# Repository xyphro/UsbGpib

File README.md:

# Table of contents

:newspaper: [Latest updates](Updates.md)
<br> :hammer: [Buy it or build it](#buy-it-or-build-it)
<br> :wave: [UsbGpib Introduction](#usbgpib-introduction)
<br> :house: [Housing / Enclosure](#housings)
<br> :computer: [Software](#software)
<br> &nbsp; &nbsp; :electric_plug: [Using the device](#using-the-device)
<br> &nbsp; &nbsp; :gear: [Setting and getting parameters](#setting-parameters)
<br> :heavy_check_mark: [Testing status](#testing-status)
<br> :notebook: [Tutorials](Tutorials/README.md) <- **New!**
<br> :heart: [Support the Project](#support-the-project)

# Summarized latest updates

For detailed visibility look under the Latest update link above!

[18th Apr 2026]: **Released Firmware V2.4: Added support for multiple GPIB devices**

[18th Apr 2026]: **Added some updated notes on GPIBee**

[07th Mar 2026]: **USbGpib V2 back in Stock on Elecrow**  

[07th Mar 2026]: **10 UsbGpib V3 == GPIBee prototypes ready for testing**

# Next version update USBGpib V3 

**UsbGpib V3 has a Name - Introducing GPIBee**

...and as you’ll see in the picture: The beauties are ready!

After months of development, redesigns, loosing hair on fixing SW bugs and teasing the new Ethernet + PoE capabilities, the next generation of UsbGpib finally has its official identity. From this point forward, UsbGpib V3 will be known as GPIBee - a compact, fast, and delightfully capable little worker that's ready to buzz around your lab equipment.

PoE is fully operational, VXI-11 supports multiple simultaneous connections, and USB High-Speed is performing flawlessly - on MY bench. Which does not mean (yet) on everybody elses bench. Testing is by multiple people is always very important!

I now have ten GPIBee prototypes fully assembled and sitting proudly on my desk. These units will soon head out to the first wave of beta testers who’ve been following the journey and are eager to put them through real‑world use.
I had hoped to start shipping next week, but with Embedded World taking up my entire schedule, distribution will begin shortly after I'm back. The excitement doesn't slow down - it just builds a little more.

Thank you all for the incredible support, feedback, and enthusiasm.

GPIBee is about to take its first flight, and you're part of the swarm that made it possible.
Stay tuned - beta testing starts soon, and the prototypes look fantastic.

## GPIBee update 18th April: 

The first prototypes have been shipped, and internal testing is already well advanced.  
Across all protocols, read performance shows a **3.5× to 5× speed increase**, and this is **without** any dedicated speed-optimization work applied yet.

## Communication Modes

### USB Interface

GPIBee supports three independent USB-based communication modes:

1. **Network mode**  
   GPIBee exposes a USB-based Ethernet interface. An IP address is assigned automatically, enabling true plug-and-play operation.  
   - Full **VXI-11** support  
   - Integrated **web server** providing configuration pages, a GPIB command console, and the complete manual matching the currently installed firmware  
   - Ideal for multi-device setups and remote control - it should be considered as the first Goto solution in terms of USB based modes.

2. **USBTMC mode**  
   Similar to **UsbGpib V2**, but extended with additional commands, including the ability to set the target **GPIB device address** — enabling communication with multiple GPIB instruments.

3. **++ protocol mode**  
   Exposes a **USB CDC UART** implementing the popular ++ protocol, compatible with existing controllers using that protocol — but at significantly higher speed.

The USB modes are **mutually exclusive**. The active mode can be selected via the **web interface** or through internal **SCPI commands**.

### Ethernet Interface

1. **VXI-11**  
   Provides multiple logical channels, allowing communication with several GPIB devices simultaneously without manually switching addresses between commands. 
   - Proper **lock handling** for multi-client access  
   - Full **SRQ** support  
   - Full **GPIB subaddressing** support

2. **++ protocol**  
   Optional **TCP/IP** service on port **1234**, offering the same `++` protocol implementation as in USB CDC UART mode.

Both Ethernet protocols can be **active at the same time**. The Ethernet interface also exposes the same **web interface** as USB network mode, enabling GPIB transfers, configuration changes, and access to the **firmware-synchronized manual**.

## GPIBee Beta Testing Status

The current beta focus remains on **functional correctness and stability**.  
**Speed optimization** will follow next.

For testers not having received an adapter yet: Additional prototype units will be shipped soon. Handling too many testers at once would otherwise become too **time-intensive**.

---

# Buy it or build it

* Tired of tinkering? Want to skip the hassle and get straight to using your GPIB setup?  
* You’d rather spend your time using your instruments instead of assembling hardware?

Skip the soldering iron and jump straight into your GPIB workflow!

You’ve got two solid options to get a ready‑to‑run UsbGpib adapter.

## &#x1f1fa;&#x1f1f8; - United States
* If you're in the US, you can now order the UsbGpibV2 directly from several sources, including my distribution partner Binho LLC. Enjoy fast domestic shipping with no long waits, no customs paperwork, and no surprises - just quick delivery and a smooth experience: 
<br> &#x1F449; <a href="https://binho.io/test-measurement/products/usbgpib-v2/" target="_blank">https://binho.io/test-measurement/products/usbgpib-v2/</a>
<br> &#x1F449; <a href="https://www.digikey.com/short/29nqq5cz" target="_blank"> https://www.digikey.com/short/29nqq5cz</a>
<br> &#x1F449; Amazon US also has it listed, but right now no stock, but worthwhile to check it out there too.

## &#x1F30E; - Worldwide
* I’ve teamed up with Elecrow to bring you ready-to-roll GPIB-USB converters – perfect for those who want results, not a weekend project.
* These adapters come fully assembled, programmed, housed, tested, and ready to go. No fuss. No build. Just plug it in and start working.
* The Adapters match 100% the V2 version described in this repository. 
* &#x1F449; <a href="https://www.elecrow.com/xyphrolabs-gpibusb.html" target="_blank">https://www.elecrow.com/xyphrolabs-gpibusb.html</a>

Let the data flow begin!

This doesn’t mean I’m going fully commercial - far from it.
Offering pre-built adapters is simply a convenience for those who’d rather skip the build and get straight to using their gear.

All sharing, support, and collaboration will remain fully open, just as before.
This is about choice, not change!

The full design files are located in this repository in case you want to build the devices yourself.

---

# UsbGpib Introduction
Versatile, cheap, portable and robust USB to GPIB converter (USBTMC class based).

You'll find many projects like this, but this one is special (ok, everybody will claim this) :-)

V1 Hardware: 

V2 Hardware: 

If you have a lot of test equipment at home, you might know the issues: Lots of devices only have GPIB as interface and the GPIB adapters and GPIB cables on the market are very expensive and some of them even have many issues, when run under Windows 10 (device driver does not work). Or they e.g. are not able to be operated with VISA, because they are UART based, need special command sequences, ...

The adapters are also typically very long, such that they extend the overall length of your test equipment by at least 10cm (~4 inches).

Apart of the 2 very big manufacturers, other GPIB adapters, e.g. with Ethernet or also USB interface are not recognized by normal VISA providers or PyVisa, making the measurement control implementation specific for your GPIB adapter.

I've got frustrated and tried to turn it into something positive. Here a video showing the final device in action - click to view:

Some goals of the project were:
- Work based on the standard USBTMC protocol. This allows the GPIB test equipment to look like a normal USB based measurement device and work flawless with e.g. NI VISA, Labview, Matlab or PyVisa.
- Have a small length - otherwise my equipment has the risk of falling from the shelf :-) Also the USB cable should connect 90 degree angled, to make it very short. With V2 HW, the length got further reduced to the size of a GPIB connector.
- It should be cheap but still versatile (you can build a single one of these for only 14 USD!)
- It should support ALL my test equipment, from many different GPIB implementation generations and different GPIB flavors
- The Firmware should be upgradeable over USB
- It should be rock-solid (!) I don't want to end up in a very long measurement being interrupted because of a software issue of my USB GPIB converter.
- It should support additional features like serial poll, remote enabling/disabling
- If there is no GPIB device connected to the USBGpib converter, or the GPIB device is powered down, there should be no USB device visible on the PC.

All those goals are met.

---

# Hardware

## Microcontroller choice

Although I typically would prefer nowadays an ARM Cortex M0/3/4/7 controller, there is an issue with it. Available devices support only max. 3.3V supply voltages, such that there would be a requirement for a level-shifter towards the GPIB Bus.
GPIB is based on 5V (not exactly true, but a first iteration).

This limited the microcontroller choice to e.g. AVR or PIC controllers. Because of very good availability I ended up in ATMEGA32U4 controllers.
Apart of the device supporting 5V I/O voltages, it also does not require a regulator to be part of the application - it has an internal 3.3V regulator. This minimizes the full application schematic and BOM.

Apart from that, there is an excellent USB stack available [http://www.fourwalledcubicle.com/LUFA.php](http://www.fourwalledcubicle.com/LUFA.php).

The GPIB side of the schematic can be directly connected to the ATMega32U4 IO pins. The IO pins from the microcontroller side are only set to 2 different states: Tri-state (input) or output LOW, to talk over GPIB.

## Component sourcing

All components are easy to source, so I only specify the potential critical ones:

- 16 MHz Crystal: Farnell 2853867 - MCSJK-7E-16.00-8-30-100-B-30 
- REV 1 GPIB connector: Farnell 2421095 - NORCOMP 112-024-113R001. For REV 2 use a straight 24P male solder type connector e.g. from AliExpress.
- USB connector for V1 HW: Farnell 2668483 - Amphenol ICC 61729-1011BLF
- USB connector for V2 HW: Best is to look on AliExpress for 57 series 24P connector as a starting point.

## PCB

The PCB can be ordered at nearly any PCB pool production service (e.g. 10 PCBs for 2 USD + shipping). The gerber files are included in the "HW/Gerber files" subdirectory.

## Mounting the PCB & Flashing the firmware

The PCB is available in 2 revisions.
- [REV 1](HW/REV1/README.md) is the most popularly used right now due to age. It has a USB Type-B connector and an L-shaped housing visible on a few photos of this page.
- [REV 2](HW/REV2/README.md) has some improvements like being smaller, better fit and USB Type-C connector.
- A REV 3 is upcoming. It will be a major redesign with more speed, Ethernet and power over Ethernet support, but the same DNA: Standard protocols being used and ensure compatibility and stability!

Choose whatever you prefer. The software images, but also the external behavior is the same.

---

# Housings

## REV 1

I created a sophisticated 3D printable housing for this adapter. The design was made with Fusion 360. The project file + the STL files are included in the "Housing" sub directory.

The PCB fits perfectly into it. Optionally it can be fixed with 2 mounting screws (the GPIB connector has 2 threads, use 2 times 4-40 UNC x 3/8) and the TOP cover snaps onto the housing base.

I printed this using an Ender 5 3D printer with black PLA, 0.15mm layer height, 1mm wall thickness, no support.
Take care, that you rotate the TOP part of the housing by 180 degrees, so that the flat side is located on the printer bed.
Printing works fine, several iterations of the design were made to ensure good printability.
I printed so far 15 housings, without a single fail.

More information on this REV 1 can be found here: [REV 1](HW/REV1/README.md).
Note, that also the programming/build instructions moved to this location.

## REV 2

The REV 2 housing is a lot smaller, but requires 2 screws.
The housing is quite important to be able to connect and disconnect the board without breaking anything. It is key for mechanical stability of the adapter.
When operating the device without housing, take very well care when plugging in and out the board in case the GPIB connector has a very tight fit.

Information on how to build it can be found in the HW/REV 2 folder: [REV 2](HW/REV2/README.md).
Note, that also the programming/build instructions moved to this location.

---

# Software

## Source code

The source code of the Boot loader (slightly modified LUFA MassStorage Boot loader) and the main USBGPIB converter are located in the "SW" subdirectory.
At the time of publication LUFA 170418 release was used, with GCC as compiler.

Note: The Software is compatible with any HW revision in this repository. For REV 1 and REV 2 hardware you don't need different SW images.

## Binaries

For those, that just want to create their own device, I've included the binary output in the "SW/binaries" subdirectory.

---

# Using the device

## USB enumeration

You might be surprised initially, that the device does not show up in your device manager (or lsusb), when you connect only the USB side. This is a feature, not a bug (really!).
Only, if a GPIB device is connected, you can see the device on your PC too.

The reason behind the feature is simple: Instead of having a standard GPIB wiring, where you have a single GPIB controller and lots of GPIB devices interconnected, USBGPIB supports only a direct connection of the USBGPIB device to your measurement device. If you have like me e.g. 14 Instruments you don't want all to show up in the device manager, if the measurement device itself is powered down - you won't anyway be able to communicate with a powered down device.

When USB and the GPIB side is connected, the device enumerates. The USBGPIB device reads out the ID of the instrument and constructs a unique USB Serial number out of it. It is thus easily possible to assiate multiple connected USBGPIB devices with the measurement instrument.

The VISA ressource name is constructed from this USB Serial number. You can identify easily e.g. in NiMax, which device is connected:

If you connect your USBGPIB device afterwards to another GPIB measurement device, it will disconnect and connect with a new serial number string, matching the other GPIB device *IDN? response again.

## GPIB settings on your measurement device

GPIBUSB does probe all GPIB primary addresses (and secondary address 0) for presence of a GPIB Talker/listener. It is thus not required to set a specific GPIB address - GPIBUSB will find it itself.

The only importance setting on the measurement device is, that the GPIB interface is enabled, which is typically the case.

## LED indicator

The LED indicates different states:

LED blinking: The USBGPIB converter is connected to a measurement instrument, it is powered off or its GPIB port is disabled. In this state, the device is also not connected to USB and will not show up in the device manager or lsusb.
LED on: The device is connected to a measurement device and GPIB communication possible. It is also accessible over USB
LED off: The device is not connected over USB, or the PC powered off :-)

## Controlling GPIB devices

As this converter implements the standard USBTMC Test and measurement class, you can control your instrument from ANY of the normal VISA tools. I tried so far R&S VISA and NI Visa, using Python and Matlab to talk to the devices.

# Testing status

This project is actively maintained since more than 6 years and I personally consider it as very stable. It is proven by multiple users to operate on MacOSX, Linux and Windows and measurement equipment from several decades.

In general I take bug reports very serious and want to "fix them all". In case you don't get an answer on-time on items you report in the issues section, please write me: Xyphro@gmail.com. 
I often miss seeing issue reports very quickly, as I don't get an email once they are filed.

## Sucessfully tested measurement equipment:

Below list is equipment I mainly myself tested. Many other users have other measurement equipment proven in use already.

- R&S FSEM30
- R&S SMIQ03
- R&S CMU200
- R&S SMW200A
- R&S FSW
- R&S FSV
- Keithley 199 multimeter
- HP 34401 DMM from different generations / with different FW versions
- HP 3325A synthesizer/frequency generator
- HP 3457A multimeter
- Agilent E4406A VSA transmitter tester
- Tektronix TDS7104 Digital Phosphor Oscilloscope
- HP 8596A spectrum analyzer
- Agilent E3648A dual power supply

## Scenarious

- It works under all popular operating systems like Windows 7 and 10, 11, Linux and MacOSX
- USB1.1, USB2.0 and USB3.x ports tested, with and without USB HUB in between.
- The connection stays responsive, when power cycling the PC, or hibernating/sleeping it
- Different connection cycles (GPIB side connected first, USB side connected first, swapping GPIB side equipment, ...)
- Extensive testing of timeout scenarious. E.g. making an illegal query and testing, if the USBTMC handles the timeouts properly. This was a very tricky part to get right.
- Tested special transfer modes. E.g. capturing screenshots from different equipment is usually something, which will drive other GPIB adapters to the limits, because binary data of unknown length needs to be transported successfully.

# Setting Parameters

The firmware version from 13th January 2024 onwards has the ability for human readable text base configuration of several parameters.
The previous methods are still supported, but won't be further documented. You can look them back in the history of this file.

The command parser is quite simple. For that reason follow the exact syntax as shown below. 
Don't add extra spaces or make other modifications or concatenate commands.

## Read termination method

While most GPIB interfaces use the hardware signal EOI to signal the end of a message, not all old equipment supports it. Some older instruments even don't have the EOI pin hardware wise wired and use \r or \n termination.

The USB-TMC standard allows to set the read termination. While in firmware versions before < 2.0 I did not enable that method, it is now finally supported with standard compliance.

I document here the older method (using pulse indicator request), but I add also the newer methods which are 100% UsbTmc compliant and portable across different equipments. You can choose which ones to use, but in some cases pulse indicator requests can be difficult to issue, for which reason it is likely better to use the standard compliant method.

### Set read termination to CR (\r):
(old method)
```
dev.control_in(0xa1, 0x40, 0, 0, 1); # USBTMC pulse indicator request (enables internal command processing)
dev.write('!term cr')
```
Above setting is volatile. To make this a permanent setting call the below mentioned "!term store" command.

(prefered method) Alternatively you can set the termination directly with visa means, e.g. using PyVisa:
```
dev.set_visa_attribute(visa.constants.VI_ATTR_TERMCHAR_EN, True)
dev.set_visa_attribute(visa.constants.VI_ATTR_TERMCHAR, ord('\r') )
```

### Set read termination to LF (\n):
(old method)
```
dev.control_in(0xa1, 0x40, 0, 0, 1); # USBTMC pulse indicator request (enables internal command processing)
dev.write('!term lf')
```
Above setting is volatile. To make this a permanent setting call the below mentioned "!term store" command.

(prefered method) Alternatively you can set the termination directly with visa means, e.g. using PyVisa:
```
dev.set_visa_attribute(visa.constants.VI_ATTR_TERMCHAR_EN, True)
dev.set_visa_attribute(visa.constants.VI_ATTR_TERMCHAR, ord('\n') )
```

### Set read termination to EOI only (default setting):
(old method) 
```
dev.control_in(0xa1, 0x40, 0, 0, 1); # USBTMC pulse indicator request (enables internal command processing)
dev.write('!term eoi')
```
Above setting is volatile. To make this a permanent setting call the below mentioned "!term store" command.

(prefered method) Alternatively you can set the termination directly with visa means, e.g. using PyVisa:
```
dev.set_visa_attribute(visa.constants.VI_ATTR_TERMCHAR_EN, False)
dev.set_visa_attribute(visa.constants.VI_ATTR_TERMCHAR, ord('\0') )
```

### Save readtermination setting in eeprom (make them non-volatile)
```
dev.control_in(0xa1, 0x40, 0, 0, 1); # USBTMC pulse indicator request (enables internal command processing)
dev.write('!term store')
```

Above relates to the "old non prefered method". In general it is a good idea to set the read termination volatile and use the above suggested methods highlighted with (prefered method).

### Query current termination setting from device
```
dev.control_in(0xa1, 0x40, 0, 0, 1); # USBTMC pulse indicator request (enables internal command processing)
print(dev.query('!term?'))
```
This returns a text string containing "lf", "cr" or "eoi"

## Multi-device support - Setting the GPIB device target address

Since Firmware version V2.4 USBGpib allows supporting multiple instruments.

While the USBTMC protocol allows only setting a single device to be addressed and composite USB devices are not well supported by all VISA implementations, I decided to add a command to set the address of the GPIB device which is addressed.

There is a minor limitation of this approach, which is that service request SRQ handling is only done properly to the currently selected GPIB device.
Another one is, that users shall never forget to set the GPIB address to the correct setting before issuing a command.

### Setting a primary address only

Substitute the text <Primary_address> with a number from 1 to 30 to set the primary address of the new GPIB device to talk to in following GPIB transactions

```
dev.control_in(0xa1, 0x40, 0, 0, 1);
dev.write('!addr <Primary_address>')
```

### Setting a primary + secondary address

Substitute the text <Primary_address> with a number from 1 to 30 to set the primary address and <Secondary_address> with a number from 0..6 or 96..102 of the new GPIB device to talk to in following GPIB transactions.
Note, that not the full subaddress range of 0..31 or 96..127 is supported as of now - this requires a bit more work. Most common device with subaddresses like R&S CMU200 only are well covered with that current range.

```
dev.control_in(0xa1, 0x40, 0, 0, 1);
dev.write('!addr <Primary_address> <Secondary_address>')
```
### Python wrapper example code for GPIB address setting

```
import pyvisa as visa
dev = 'USB0::0x03EB::0x2065::GPIB_22_14236333938351C00011::INSTR'
rm = visa.ResourceManager()
dev = rm.open_resource(dev, open_timeout=1000)

def set_gpib_addr(primary_address, secondary_address = None):
    dev.control_in(0xa1, 0x40, 0, 0, 1);
    if secondary_address is None:
        dev.write('!addr %d' % primary_address);
    else:
        dev.write('!addr %d %d' % (primary_address, secondary_address));
    
# Address CMU200, which is for me on primary address 1, secondary address 0
set_gpib_addr(1, 0)
print(dev.query('*IDN?'))

# address HP3457A on primary GPIB address 22
set_gpib_addr(22)
dev.write('END,ALWAYS')
print(dev.query('ID?'))
```

This code results in my current testsetup with CMU200 and HP3457A in this output:

```
Rohde&Schwarz,CMU 200-1100.0008.02,xxxxxx,V5.22

HP3457A
```

## AutoID setting

Default wise the GPIB adapter tries during power on of the instrument to query using *IDN? or ID? commands the instrument name automatically.
This is used to build the USB serial number, which finally gets part of the VISA ressource string.

Not all instruments support this *IDN / ID? query. For this reason this feature can be turned off.
The serial number will then be built based on the GPIB address of the instrument.

### Turn AutoID feature off
```
dev.control_in(0xa1, 0x40, 0, 0, 1); # USBTMC pulse indicator request (enables internal command processing)
dev.write('!autoid off')
```
This setting is stored in eeprom = non volatile memory, so will survive a power cycle

### Turn AutoID feature on
```
dev.control_in(0xa1, 0x40, 0, 0, 1); # USBTMC pulse indicator request (enables internal command processing)
dev.write('!autoid on')
```
This setting is stored in eeprom = non volatile memory, so will survive a power cycle

### turn auto ID on with delay

Some instruments need after turn on some seconds before GPIB is responsive.

With below 3 settings you can set a delay which is applied before the instrument ID is queried after power on.
Note that it will take then also more time, before the USB device is recognized by the PC.

Also this setting is non-volatile.

Delay 5 seconds:
```
dev.control_in(0xa1, 0x40, 0, 0, 1); # USBTMC pulse indicator request (enables internal command processing)
dev.write('!autoid slow')
```

Delay 15 seconds:
```
dev.control_in(0xa1, 0x40, 0, 0, 1); # USBTMC pulse indicator request (enables internal command processing)
dev.write('!autoid slower')
```

Delay 30 seconds:
```
dev.control_in(0xa1, 0x40, 0, 0, 1); # USBTMC pulse indicator request (enables internal command processing)
dev.write('!autoid slowest')
```

### read autoid setting

```
dev.control_in(0xa1, 0x40, 0, 0, 1); # 
print(dev.query('!autoid?'))
```
Returns as text string either: "off", "on", "slow", "slower" or "slowest".

## Firmware version

Finally I implemented a command to query the USB adapters firmware version :-)

```
dev.control_in(0xa1, 0x40, 0, 0, 1); # USBTMC pulse indicator request (enables internal command processing)
print(dev.query('!ver?'))
```

## Shorten ressource strings (Matlab)

A user discovered that Matlab has a limitation in the VISA ressource string length and shared a pull request to reduce the length.
I expose this now first time in the baseline firmware with the following options.

This setting is stored in eeprom = non volatile.

### Limit the USB serial number to a length of 20 characters
```
dev.control_in(0xa1, 0x40, 0, 0, 1); # USBTMC pulse indicator request (enables internal command processing)
dev.write('!string short')
```

### disable limitation of USB serial number length (default behavior)
```
dev.control_in(0xa1, 0x40, 0, 0, 1); # USBTMC pulse indicator request (enables internal command processing)
dev.write('!string normal')
```

### query the string length setting.
```
dev.control_in(0xa1, 0x40, 0, 0, 1); # USBTMC pulse indicator request (enables internal command processing)
print(dev.query('!string?'))
```

This returns as text string either "normal" or "short".

## reset the adapter
```
dev.control_in(0xa1, 0x40, 0, 0, 1); 
dev.write('!reset')
```

Do a reset of the adapter. Note that due to the reset you have to close the visa session and start a new one as the device re-enumerates on the USB.

---

# Support the project

Or support by buying a fully prebuilt adapter at: <a href="https://www.elecrow.com/xyphrolabs-gpibusb.html" target="_blank">https://www.elecrow.com/xyphrolabs-gpibusb.html</a>

In general any email, post or feedback is also very valuable, and don't feel bad if you don't use the support options :-)
Feel free to contact me at Xyphro@gmail.com

---

This page is from XyphroLabs UsbGpib project: <a href="https://github.com/xyphro/UsbGpib" target="_blank">https://github.com/xyphro/UsbGpib</a>

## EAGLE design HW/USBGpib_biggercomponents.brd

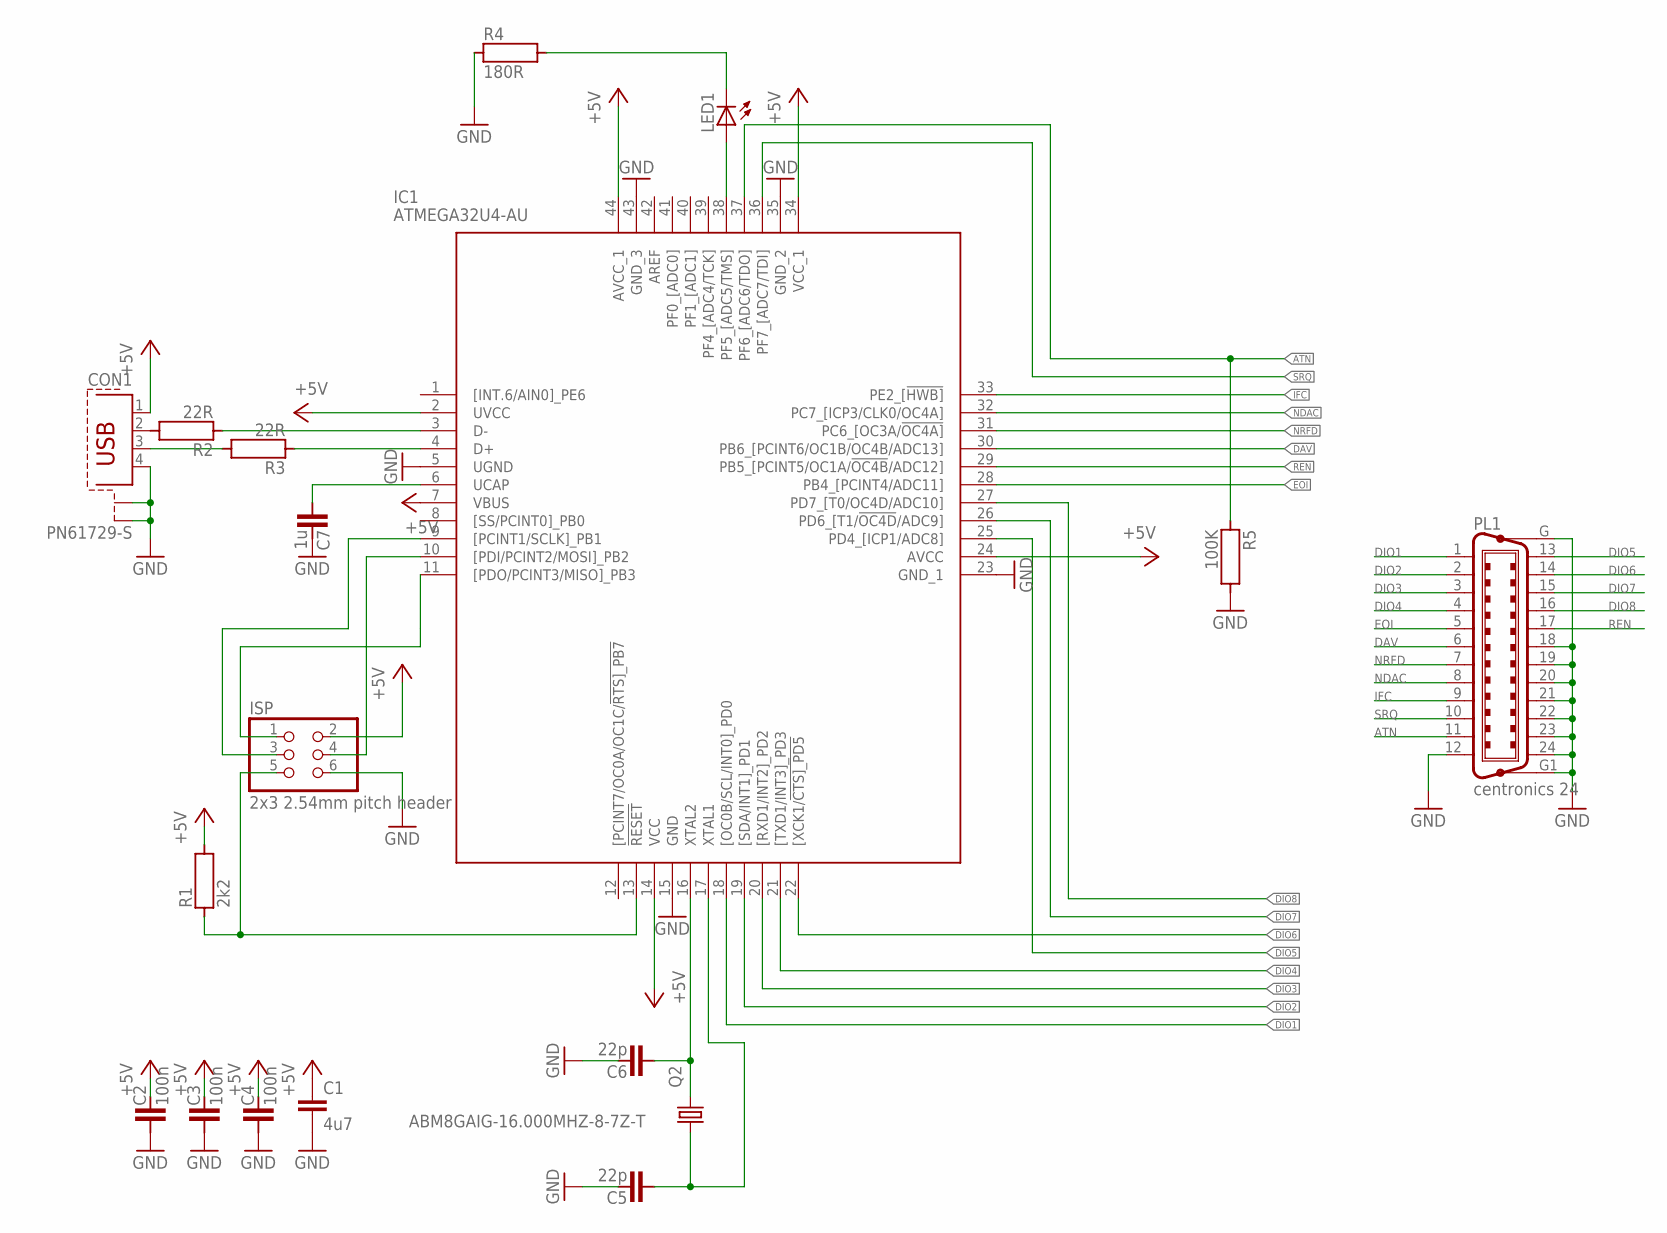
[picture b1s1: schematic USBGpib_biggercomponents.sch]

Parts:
C1: 4u7; C0805
C2, C3, C4: 100n; C0603
C5, C6: 22p; C0603
C7: 1u; C0603
CON1: PN61729-S
IC1: ATMEGA32U4-AU; QFP80P1200X1200X120-44N
ISP: 2x3 2.54mm pitch header; 2X03
LED1: LEDCHIPLED_1206; CHIPLED_1206
PL1: centronics 24; 24HP_MALE
Q2: ABM8GAIG-16.000MHZ-8-7Z-T; 3.2X2.5_KX-7
R1: 2k2; R0603
R2, R3: 22R; R0603
R4: 180R; R0603
R5: 100K; R0603

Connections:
+5V: C1.1, C2.2, C3.2, C4.2, CON1.1, IC1.2 (UVCC), IC1.7 (VBUS), IC1.14 (VCC), IC1.24 (AVCC), IC1.34 (VCC_1), IC1.44 (AVCC_1), ISP.2, R1.2
ATN: IC1.37 (PF6_[ADC6/TDO]), PL1.11, R5.1
DAV: IC1.30 (PB6_[PCINT6/OC1B/OC4B/ADC13]), PL1.6
DIO1: IC1.18 ([OC0B/SCL/INT0]_PD0), PL1.1
DIO2: IC1.19 ([SDA/INT1]_PD1), PL1.2
DIO3: IC1.20 ([RXD1/INT2]_PD2), PL1.3
DIO4: IC1.21 ([TXD1/INT3]_PD3), PL1.4
DIO5: IC1.25 (PD4_[ICP1/ADC8]), PL1.13
DIO6: IC1.22 ([XCK1/!CTS]_PD5), PL1.14
DIO7: IC1.26 (PD6_[T1/!OC4D!/ADC9]), PL1.15
DIO8: IC1.27 (PD7_[T0/OC4D/ADC10]), PL1.16
D_N: IC1.3 (D-), R2.1
D_P: IC1.4 (D+), R3.1
EOI: IC1.28 (PB4_[PCINT4/ADC11]), PL1.5
GND: C1.2, C2.1, C3.1, C4.1, C5.2, C6.2, C7.2, CON1.4, CON1.S1, CON1.S2, IC1.5 (UGND), IC1.15 (GND), IC1.23 (GND_1), IC1.35 (GND_2), IC1.43 (GND_3), ISP.6, PL1.12, PL1.18, PL1.19, PL1.20, PL1.21, PL1.22, PL1.23, PL1.24, PL1.G, PL1.G1, R4.1, R5.2
IFC: IC1.33 (PE2_[!HWB]), PL1.9
unnamed: C6.1, IC1.16 (XTAL2), Q2.3 (2)
unnamed: C5.1, IC1.17 (XTAL1), Q2.1
unnamed: C7.1, IC1.6 (UCAP)
unnamed: CON1.2, R2.2
unnamed: CON1.3, R3.2
unnamed: IC1.13 (!RESET), ISP.5, R1.1
unnamed: LED1.C, R4.2
unnamed: IC1.10 ([PDI/PCINT2/MOSI]_PB2), ISP.4
unnamed: IC1.9 ([PCINT1/SCLK]_PB1), ISP.3
unnamed: IC1.11 ([PDO/PCINT3/MISO]_PB3), ISP.1
unnamed: IC1.38 (PF5_[ADC5/TMS]), LED1.A
NDAC: IC1.32 (PC7_[ICP3/CLK0/OC4A]), PL1.8
NRFD: IC1.31 (PC6_[OC3A/!OC4A]), PL1.7
REN: IC1.29 (PB5_[PCINT5/OC1A/!OC4B!/ADC12]), PL1.17
SRQ: IC1.36 (PF7_[ADC7/TDI]), PL1.10

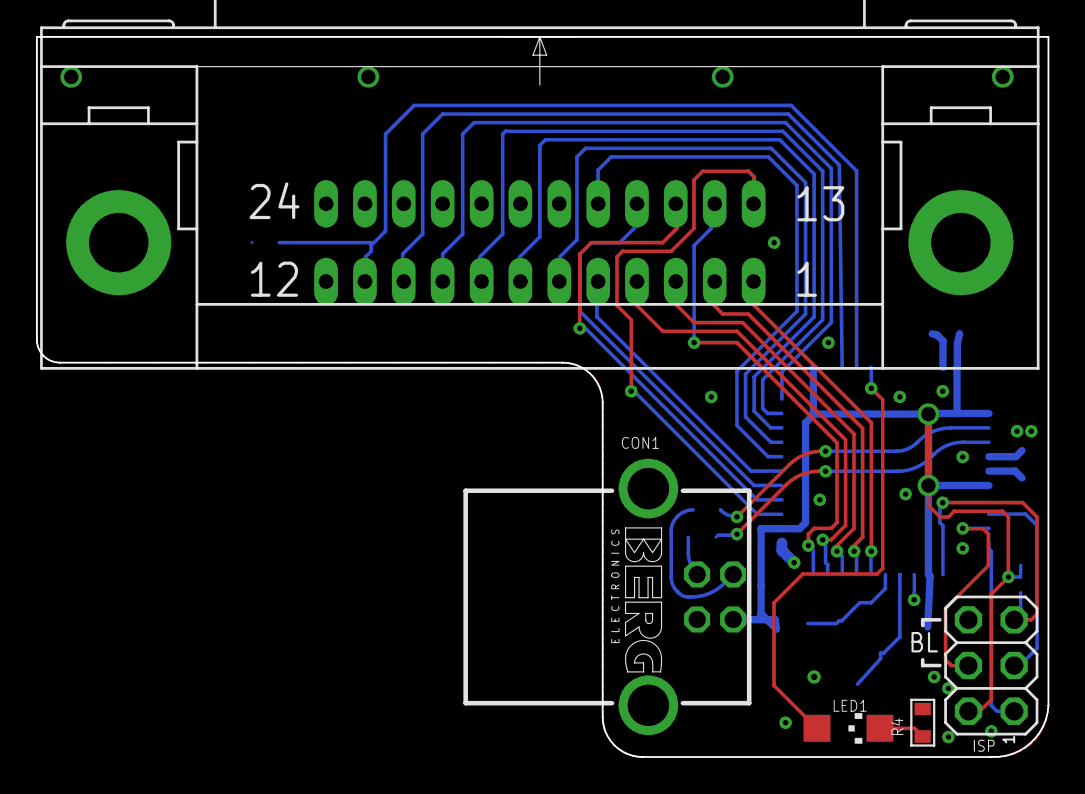
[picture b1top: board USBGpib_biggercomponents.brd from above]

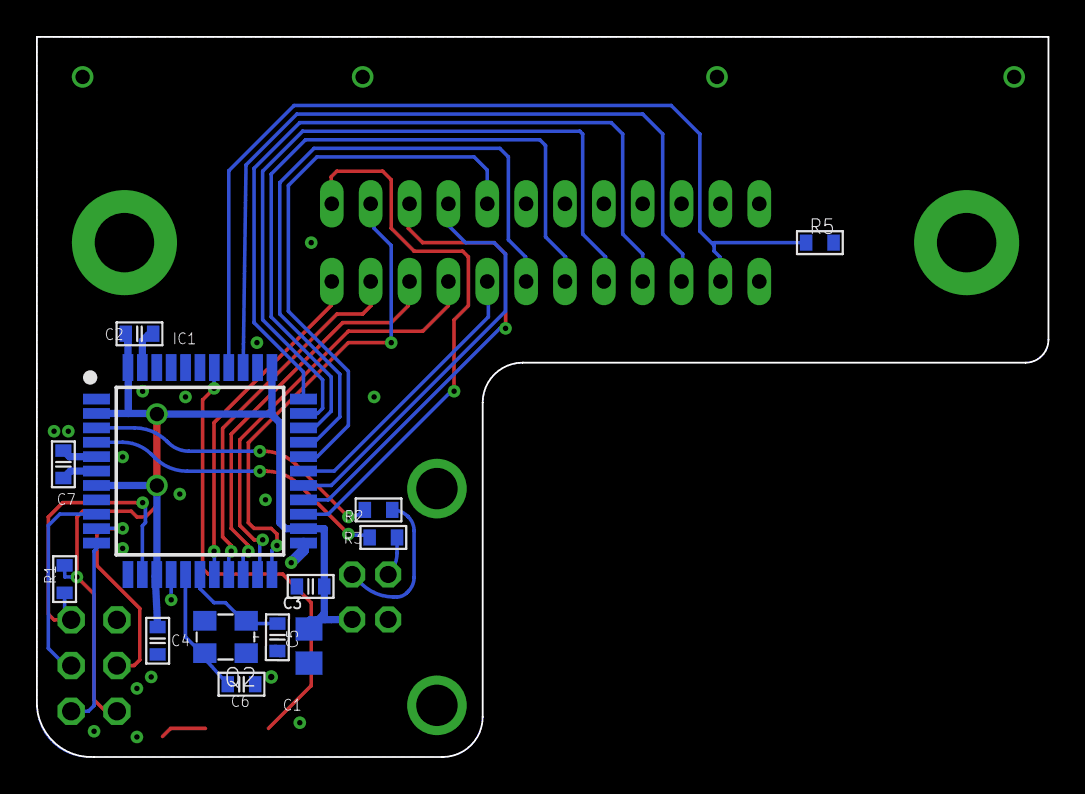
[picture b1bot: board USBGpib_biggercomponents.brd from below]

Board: 2 copper layers, 56.2 x 40.0 mm, 18 parts (13 on the bottom side), 31 nets.

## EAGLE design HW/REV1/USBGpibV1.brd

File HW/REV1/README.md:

# xyphro UsbGpib HW REV 1

This is the original HW design.

It comes in 2 flavors:
- An eagle design which is the root of all designs and my own (xyphro) design.
- A user contributed Kicad design which is also confirmed working correctly.

The [software](../../SW) will always stay the same, no matter if REV1 or REV 2.

## Assembly process

All files related to HW are located in this folder. Gerber file, BOM, Kicad design files.

## preparing the PCB

Mount all components on the PCB. For REV 1 you can assemble the whole design before putting it together.
I mention this explicitely, because for REV 2 it makes sense to mount the GPIB connector only at a later stage of assembly process.

### Flashing the Microcontroller first time

For initial programming an AVR ISP adapter is needed to program the "Bootloader.hex" file.

It is very important, that the Fuses of the AVR are programmed.

Here an example how to program the bootloader using avrdude (using usbasp programmer):
avrdude -c usbasp -p m32u4 -e -Ulock:w:0xFF:m -Uefuse:w:0xcb:m -Uhfuse:w:0xd8:m -Ulfuse:w:0xde:m

avrdude -c usbasp -p m32u4 -U flash:w:BootLoader.hex

To program bootloader and application image at the same time using AvrDude, you can use this command:
..\avrdude -c usbasp -p m32u4 -e -Ulock:w:0x3F:m -Uefuse:w:0xcb:m -Uhfuse:w:0xd8:m -Ulfuse:w:0xde:m -U flash:w:TestAndMeasurement.hex -U flash:w:BootLoader.hex

Note, that some programmers use a quite high clock frequency on the programming interface. In case of failures try to decrease the SCK clock frequency!

After programming the file, disconnect and connect the device and a USB drive will show up. Copy the TestAndMeasurement.bin file to this USB drive - ideally using the command line. Example: `copy TestAndMeasurement.bin F:\FLASH.BIN`.
On Linux, there is a bug with the LUFA mass storage that means it is required to use `dd if=TestAndMeasurement.bin of=/mnt/FLASH.BIN bs=512 conv=notrunc oflag=direct,sync`.

When done, disconnect and connect USB again and you're ready to use it!

## Building the whole thing together
Preparation:
- Mount the PCB EXCLUDING the GPIB connector.
- Print the housings located in [this folder](../../Housing/Rev1). I print them using 1mm bottom/top/wall thickness, 0.16mm layer height and 30% infil. On my older Ender 5 printer a print takes about 2.5 hours.

Assembly is easy: Insert the fully mounted PCB into the power part of the housing.

Then snap on the top part of the housing. Done :-)

# Updating the firmware at later stages

To enter the boot loader at later stages for updates, short circuit the 2 pins of the ISP header, as shown in below picture for about 3 seconds:

Afterwards, a USB drive will show up and you can copy the firmware again to the device, as described in the previous section.

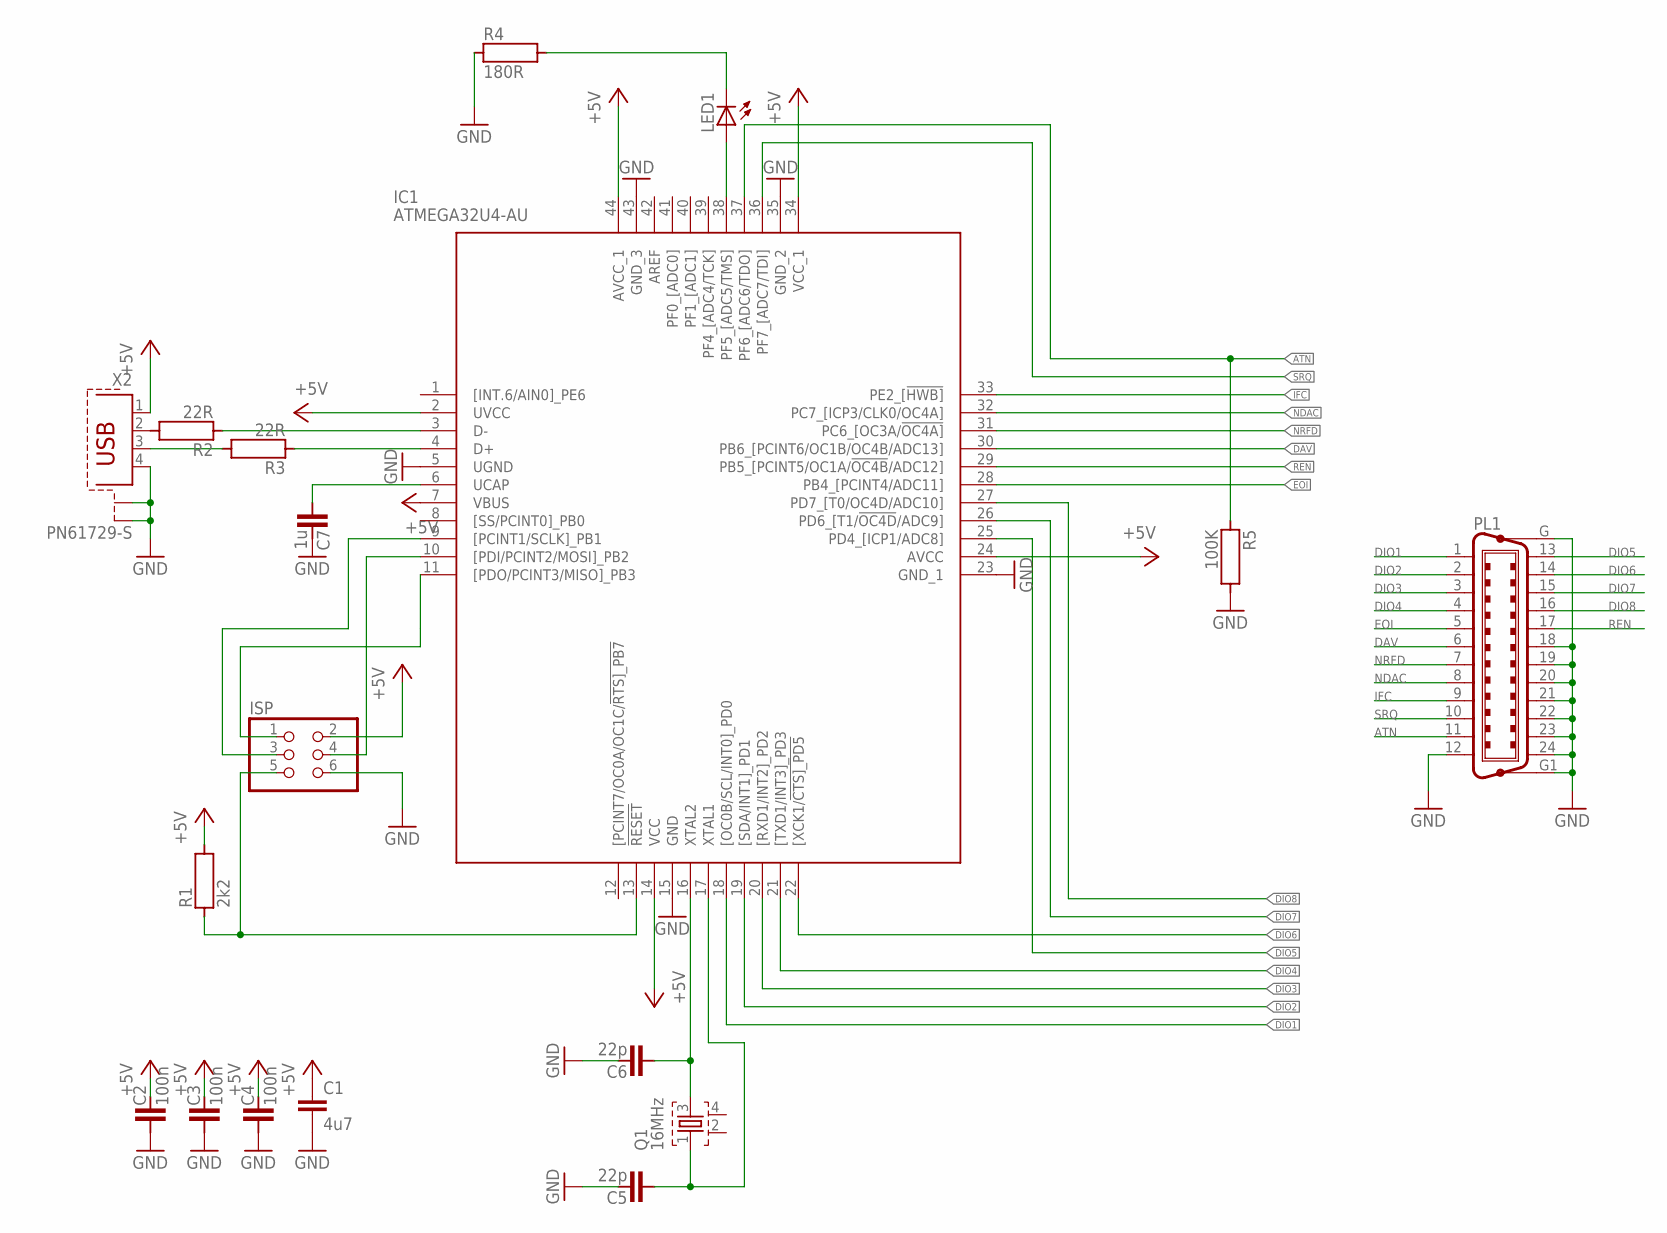
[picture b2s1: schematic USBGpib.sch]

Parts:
C1: 4u7; C1210
C2, C3, C4: 100n; C0402
C5, C6: 22p; C0402
C7: 1u; C0603
IC1: ATMEGA32U4-AU; QFP80P1200X1200X120-44N
ISP: PINHD-2X3; 2X03
LED1: LEDCHIPLED_1206; CHIPLED_1206
PL1: C24HPMALE; 24HP_MALE
Q1: 16MHz; FA-20H
R1: 2k2; R0402
R2, R3: 22R; R0402
R4: 180R; R0402
R5: 100K; R0402
X2: PN61729-S

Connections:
+5V: C1.1, C2.2, C3.2, C4.2, IC1.2 (UVCC), IC1.7 (VBUS), IC1.14 (VCC), IC1.24 (AVCC), IC1.34 (VCC_1), IC1.44 (AVCC_1), ISP.2, R1.2, X2.1; also elsewhere on the board
ATN: IC1.37 (PF6_[ADC6/TDO]), PL1.11, R5.1; also elsewhere on the board
DAV: IC1.30 (PB6_[PCINT6/OC1B/OC4B/ADC13]), PL1.6; also elsewhere on the board
DIO1: IC1.18 ([OC0B/SCL/INT0]_PD0), PL1.1; also elsewhere on the board
DIO2: IC1.19 ([SDA/INT1]_PD1), PL1.2; also elsewhere on the board
DIO3: IC1.20 ([RXD1/INT2]_PD2), PL1.3; also elsewhere on the board
DIO4: IC1.21 ([TXD1/INT3]_PD3), PL1.4; also elsewhere on the board
DIO5: IC1.25 (PD4_[ICP1/ADC8]), PL1.13; also elsewhere on the board
DIO6: IC1.22 ([XCK1/!CTS]_PD5), PL1.14; also elsewhere on the board
DIO7: IC1.26 (PD6_[T1/!OC4D!/ADC9]), PL1.15; also elsewhere on the board
DIO8: IC1.27 (PD7_[T0/OC4D/ADC10]), PL1.16; also elsewhere on the board
EOI: IC1.28 (PB4_[PCINT4/ADC11]), PL1.5; also elsewhere on the board
GND: C1.2, C2.1, C3.1, C4.1, C5.2, C6.2, C7.2, IC1.5 (UGND), IC1.15 (GND), IC1.23 (GND_1), IC1.35 (GND_2), IC1.43 (GND_3), ISP.6, PL1.12, PL1.18, PL1.19, PL1.20, PL1.21, PL1.22, PL1.23, PL1.24, PL1.G, PL1.G1, R4.1, R5.2, X2.4, X2.S1, X2.S2; also elsewhere on the board
IFC: IC1.33 (PE2_[!HWB]), PL1.9; also elsewhere on the board
unnamed 14: C6.1, IC1.16 (XTAL2), Q1.3; also elsewhere on the board
unnamed 15: C5.1, IC1.17 (XTAL1), Q1.1; also elsewhere on the board
unnamed 16: C7.1, IC1.6 (UCAP); also elsewhere on the board
unnamed: R2.2, X2.2
unnamed 18: IC1.3 (D-), R2.1; also elsewhere on the board
unnamed 19: IC1.4 (D+), R3.1; also elsewhere on the board
unnamed: R3.2, X2.3
unnamed 21: IC1.13 (!RESET), ISP.5, R1.1; also elsewhere on the board
unnamed: LED1.C, R4.2
unnamed 23: IC1.10 ([PDI/PCINT2/MOSI]_PB2), ISP.4; also elsewhere on the board
unnamed 24: IC1.9 ([PCINT1/SCLK]_PB1), ISP.3; also elsewhere on the board
unnamed 25: IC1.11 ([PDO/PCINT3/MISO]_PB3), ISP.1; also elsewhere on the board
unnamed 26: IC1.38 (PF5_[ADC5/TMS]), LED1.A; also elsewhere on the board
NDAC: IC1.32 (PC7_[ICP3/CLK0/OC4A]), PL1.8; also elsewhere on the board
NRFD: IC1.31 (PC6_[OC3A/!OC4A]), PL1.7; also elsewhere on the board
REN: IC1.29 (PB5_[PCINT5/OC1A/!OC4B!/ADC12]), PL1.17; also elsewhere on the board
SRQ: IC1.36 (PF7_[ADC7/TDI]), PL1.10; also elsewhere on the board

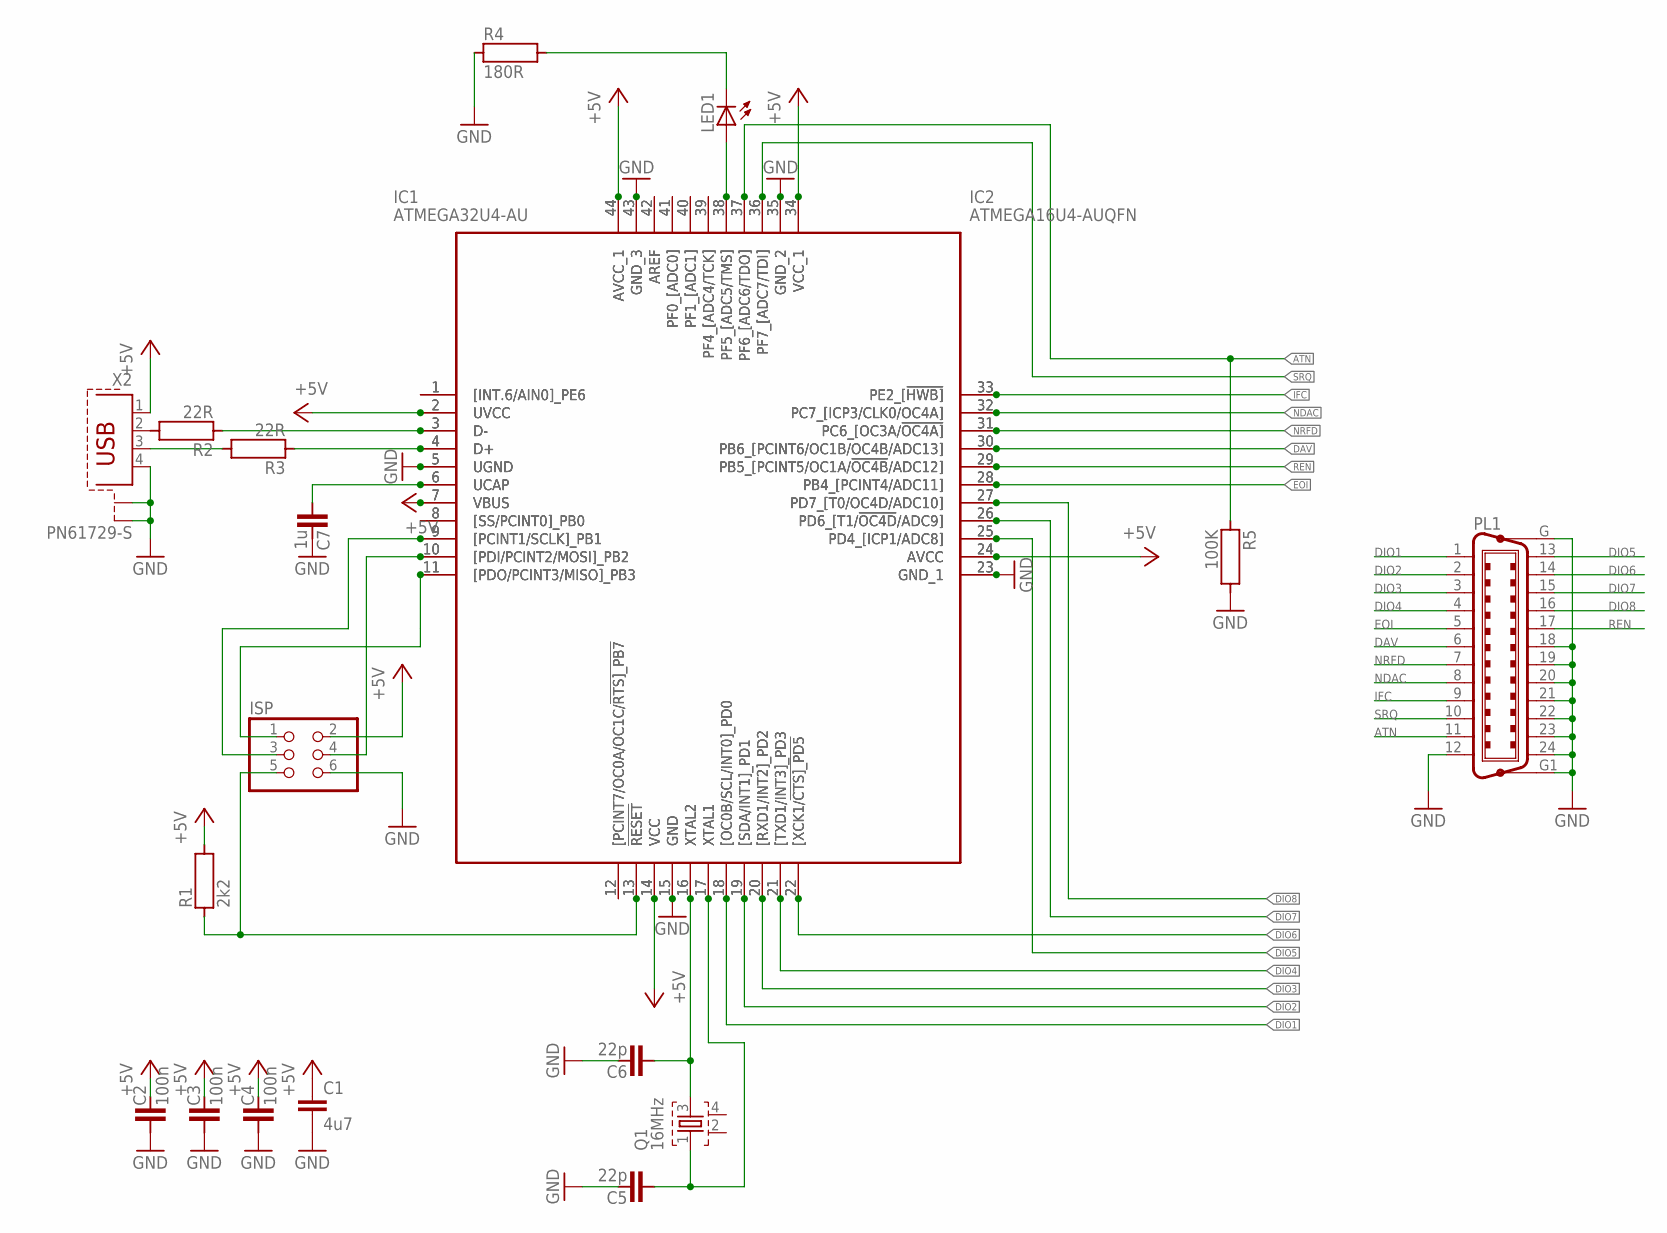
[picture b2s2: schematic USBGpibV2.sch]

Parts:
C1: 4u7; C1206
C2, C3, C4: 100n; C0603
C5, C6: 22p; C0603
C7: 1u; C0603
IC1: ATMEGA32U4-AU; QFP80P1200X1200X120-44N
IC2: ATMEGA16U4-AUQFN; QFN44
ISP: PINHD-2X3; 2X03
LED1: LEDCHIPLED_1206; CHIPLED_1206
PL1: C24HPMALE; 24HP_MALE
Q1: 16MHz; FA-20H
R1: 2k2; R0603
R2, R3: 22R; R0603
R4: 180R; R0603
R5: 100K; R0603
X2: PN61729-S

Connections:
+5V: C1.1, C2.2, C3.2, C4.2, IC1.2 (UVCC), IC1.7 (VBUS), IC1.14 (VCC), IC1.24 (AVCC), IC1.34 (VCC_1), IC1.44 (AVCC_1), IC2.2 (UVCC), IC2.7 (VBUS), IC2.14 (VCC), IC2.24 (AVCC), IC2.34 (VCC_1), IC2.44 (AVCC_1), ISP.2, R1.2, X2.1
ATN: IC1.37 (PF6_[ADC6/TDO]), IC2.37 (PF6_[ADC6/TDO]), PL1.11, R5.1
DAV: IC1.30 (PB6_[PCINT6/OC1B/OC4B/ADC13]), IC2.30 (PB6_[PCINT6/OC1B/OC4B/ADC13]), PL1.6
DIO1: IC1.18 ([OC0B/SCL/INT0]_PD0), IC2.18 ([OC0B/SCL/INT0]_PD0), PL1.1
DIO2: IC1.19 ([SDA/INT1]_PD1), IC2.19 ([SDA/INT1]_PD1), PL1.2
DIO3: IC1.20 ([RXD1/INT2]_PD2), IC2.20 ([RXD1/INT2]_PD2), PL1.3
DIO4: IC1.21 ([TXD1/INT3]_PD3), IC2.21 ([TXD1/INT3]_PD3), PL1.4
DIO5: IC1.25 (PD4_[ICP1/ADC8]), IC2.25 (PD4_[ICP1/ADC8]), PL1.13
DIO6: IC1.22 ([XCK1/!CTS]_PD5), IC2.22 ([XCK1/!CTS]_PD5), PL1.14
DIO7: IC1.26 (PD6_[T1/!OC4D!/ADC9]), IC2.26 (PD6_[T1/!OC4D!/ADC9]), PL1.15
DIO8: IC1.27 (PD7_[T0/OC4D/ADC10]), IC2.27 (PD7_[T0/OC4D/ADC10]), PL1.16
EOI: IC1.28 (PB4_[PCINT4/ADC11]), IC2.28 (PB4_[PCINT4/ADC11]), PL1.5
GND: C1.2, C2.1, C3.1, C4.1, C5.2, C6.2, C7.2, IC1.5 (UGND), IC1.15 (GND), IC1.23 (GND_1), IC1.35 (GND_2), IC1.43 (GND_3), IC2.5 (UGND), IC2.15 (GND), IC2.23 (GND_1), IC2.35 (GND_2), IC2.43 (GND_3), ISP.6, PL1.12, PL1.18, PL1.19, PL1.20, PL1.21, PL1.22, PL1.23, PL1.24, PL1.G, PL1.G1, R4.1, R5.2, X2.4, X2.S1, X2.S2
IFC: IC1.33 (PE2_[!HWB]), IC2.33 (PE2_[!HWB]), PL1.9
unnamed: C6.1, IC1.16 (XTAL2), IC2.16 (XTAL2), Q1.3
unnamed: C5.1, IC1.17 (XTAL1), IC2.17 (XTAL1), Q1.1
unnamed: C7.1, IC1.6 (UCAP), IC2.6 (UCAP)
unnamed: R2.2, X2.2
unnamed: IC1.3 (D-), IC2.3 (D-), R2.1
unnamed: IC1.4 (D+), IC2.4 (D+), R3.1
unnamed: R3.2, X2.3
unnamed: IC1.13 (!RESET), IC2.13 (!RESET), ISP.5, R1.1
unnamed: LED1.C, R4.2
unnamed: IC1.10 ([PDI/PCINT2/MOSI]_PB2), IC2.10 ([PDI/PCINT2/MOSI]_PB2), ISP.4
unnamed: IC1.9 ([PCINT1/SCLK]_PB1), IC2.9 ([PCINT1/SCLK]_PB1), ISP.3
unnamed: IC1.11 ([PDO/PCINT3/MISO]_PB3), IC2.11 ([PDO/PCINT3/MISO]_PB3), ISP.1
unnamed: IC1.38 (PF5_[ADC5/TMS]), IC2.38 (PF5_[ADC5/TMS]), LED1.A
unnamed: IC1.1 ([INT.6/AIN0]_PE6), IC2.1 ([INT.6/AIN0]_PE6)
unnamed: IC1.8 ([SS/PCINT0]_PB0), IC2.8 ([SS/PCINT0]_PB0)
unnamed: IC1.12 ([PCINT7/OC0A/OC1C/!RTS]_PB7), IC2.12 ([PCINT7/OC0A/OC1C/!RTS]_PB7)
unnamed: IC1.42 (AREF), IC2.42 (AREF)
unnamed: IC1.41 (PF0_[ADC0]), IC2.41 (PF0_[ADC0])
unnamed: IC1.40 (PF1_[ADC1]), IC2.40 (PF1_[ADC1])
unnamed: IC1.39 (PF4_[ADC4/TCK]), IC2.39 (PF4_[ADC4/TCK])
NDAC: IC1.32 (PC7_[ICP3/CLK0/OC4A]), IC2.32 (PC7_[ICP3/CLK0/OC4A]), PL1.8
NRFD: IC1.31 (PC6_[OC3A/!OC4A]), IC2.31 (PC6_[OC3A/!OC4A]), PL1.7
REN: IC1.29 (PB5_[PCINT5/OC1A/!OC4B!/ADC12]), IC2.29 (PB5_[PCINT5/OC1A/!OC4B!/ADC12]), PL1.17
SRQ: IC1.36 (PF7_[ADC7/TDI]), IC2.36 (PF7_[ADC7/TDI]), PL1.10

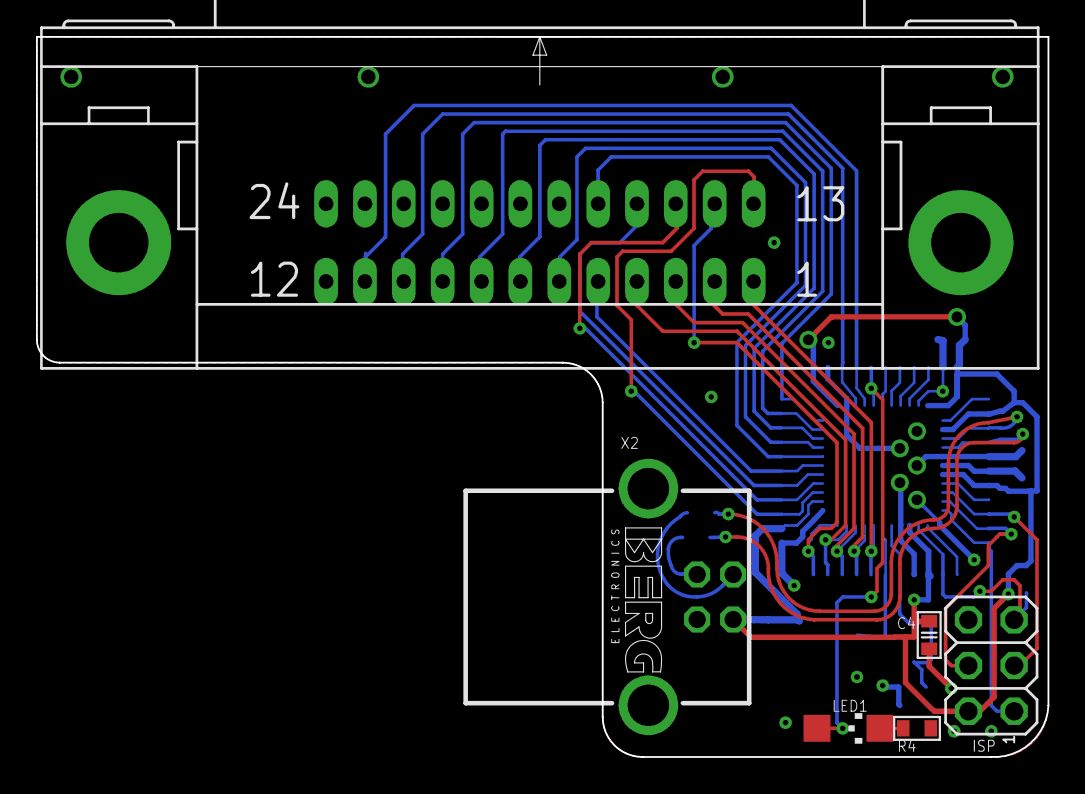
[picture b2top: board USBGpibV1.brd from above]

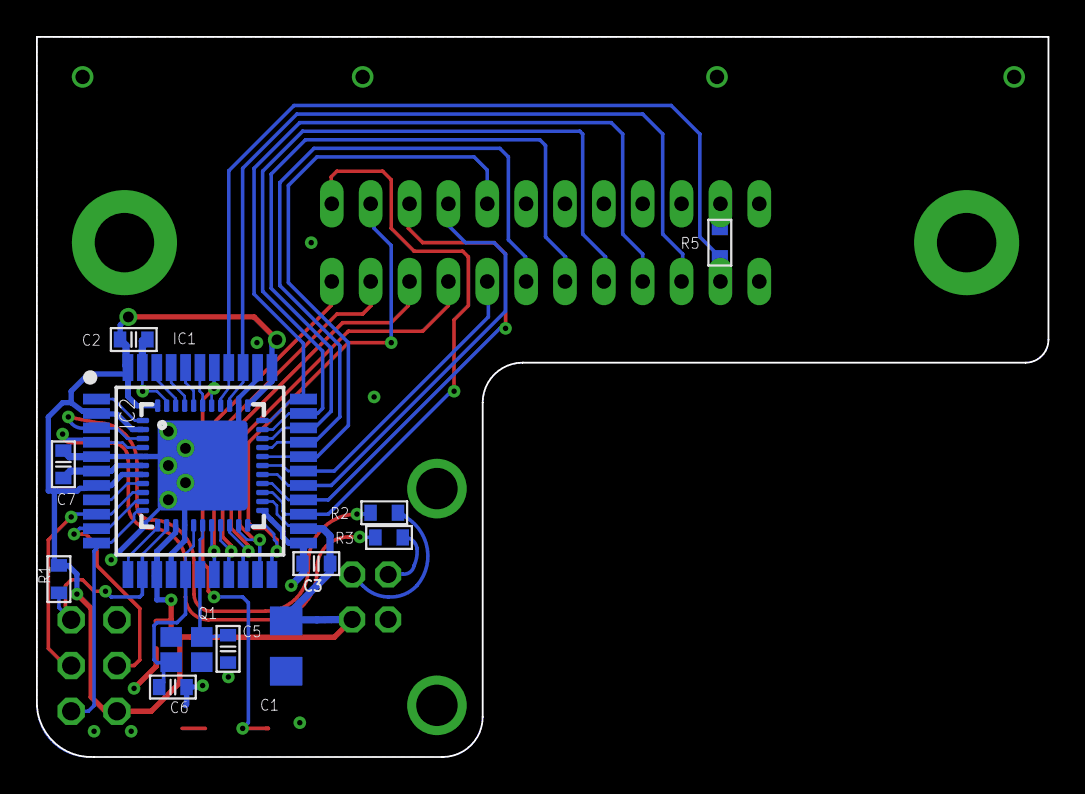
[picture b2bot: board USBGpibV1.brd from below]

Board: 2 copper layers, 56.2 x 40.0 mm, 19 parts (13 on the bottom side), 38 nets.

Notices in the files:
parts and their libraries:
crystal-geyer_V1_0: Copyright: Geyer-Electronic
